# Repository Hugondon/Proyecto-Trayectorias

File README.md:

<h1 align="center">Proyecto de Ingeniería</h1>
<h2 align="center">Generación y Monitoreo de Trayectorias 3D sobre superficies regulares para Cobots UR</h2>

<!-- <h2>Herramientas Utilizadas</h2>

1. [MATLAB R2021b](#matlab)
2. [Python 3.8.10](#python)
3. [Polyscope](#polyscope)
4. [ESP-IDF](#esp-idf)

--- -->

<h2>Herramientas Utilizadas</h2>

<details>
<summary id="matlab">MATLAB R2021b</summary>
<h4>Procesamiento de Imagenes</h4>

Este modulo fue hecho especificamente para demostraciones.  
`Proyecto-Trayectorias\Software\MATLAB\Generacion_Trayectoria\Image_processing`: Path relativo al modulo para procesamiento de imagenes.  
En la carpeta `Imagenes` guarda la imagen que quieras procesar.  
Estas son las caracteristicas que mejoran el resultado del procesamiento de imagenes:

- Formato JPEG
- Imagenes caricaturescas
- Alto contraste entre fondo y objeto de interes

En el path `Proyecto-Trayectorias\Software\MATLAB\Generacion_Trayectoria\Image_processing` abre el script `prueba_imagen.m` es donde atraves de procesamiento de imagenes algoritmos de deteccion de bordes el objeto de una imagen se convierte en una trayectoria. Las variables que debes modificar de este script son las siguientes:

- `nameImage`: nombre de la imagen en la carpeta `Imagenes` la cual se quiere procesar.
- `physicalSize_m`: longitud del lado más largo del lienzo fisico del dibujo en metros. El programa en automatico expande o comprime la imagen, esto para que la longitud del lado más largo del dibujo digital coincida con la longitud del lado más largo del lienzo fisico.
- `reductionConstant`: numero de reducion de waypoints en la trayectoria. Que el robot no ejecute una trayectoria de más de 3000 waypoints, de preferencia mantente por debajo de 1,800 waypoints. Para reducir el numero de waypoints aumenta esta variable a tu discreción. La relación se expresa con la siguiente formula:  
  $length(outputTrajectory) = \lceil {\frac {length(originalTrajectory)} {reductionConstant}}\rceil$

- `numLowPointsThreshold`: los objetos con menos de esta cantidad de waypoints son eliminados. Por lo general se usa para eliminar puntos muy pequeños de la imagen.
- `numHighPointsThreshold`: los objetos con más de esta cantidad de waypoints son eliminados. Por lo general se usa para eliminar el marco de la imagen.
- `eliminatedObject`: el ID de un objeto que se quiere eliminar en especifico.

El resultado es guardado en el archivo `waypoints.mat`.

En el path `Proyecto-Trayectorias\Software\MATLAB\Generacion_Trayectoria` abre el script `imagePlacement.m` para que puedas apreciar el tamaño del dibujo con respecto al robot. Debido a que las poses son relativas con el primer waypoint de la trayectoria no importa la posicion u orientacion. Las poses son guardadas en `trajectoryPoses.mat` para posteriormente ser simulados con el robot.

<h4>Procesamiento de Modelos CAD</h4>

En el path `Proyecto-Trayectorias\Software\MATLAB\Generacion_Trayectoria\CAD_procesing` abre el script `cad_interactive_node_selector.m` es un selector interactivo de los nodos del modelo CAD.  
En la carpeta `Parts` guarda las piezas CAD en formato CSV.  
En la linea `gm=importGeometry(msd,'Part\botella.STL')` esta el Path para exportar el modelo CAD.  
En el apartado `Generate Mesh`:

- `edgeLenght.Hmax`: maxima longitud de una arista de la malla.
- `edgeLenght.Hmin`: minima longitud de una arista de la malla.  
  Modifica `edgeLenght.Hmax` y `edgeLenght.Hmin` a tu conveniencia, aristas muy pequeñas haran el programa muy lento, aristas muy grandes haran que se pierda resolución del modelo.  
  El modelo CAD y sus parametros es guardado en `CADparameters.mat` y las poses en latrayectoria del modelo CAD junto con el modelo CAD son guardados en `processedCAD.mat`.

En el path `Proyecto-Trayectorias\Software\MATLAB\Generacion_Trayectoria` esta el script `CADplacement.m` sirve para vizualizar el robot, el modelo CAD y la trayectoria sobre la superficie del modelo CAD. Además puedes modificar la pose del modelo CAD.  
En el apartado `Modifing Processed CAD` tienes las siguientes variables para modificar la pose del modelo CAD y la trayectoria en la superficie del modelo CAD:

- `displacementVector` : representa la posicion del modelo CAD y la trayectoria.
- `rotationVector` : representa la orientacion del modelo CAD y la trayectoria.  
  Importante: la posicion y orientacion del modelo CAD y la trayectoria sobre su superficie estan ligadas modificar `displacementVector` y `rotationVector` afectara a ambas.  
  El modelo CAD y la trayectoria en su superficie son guardados en `transformedCAD.mat`, para posteriormente ser simulados con el robot.

<h4>Simulacion del Robot</h4>

En el path `Proyecto-Trayectorias\Software\MATLAB\Generacion_Trayectoria` abre el script `main.m` Toma la trayectoria deseada, calcula la cinematica inversa, grafica la trayectoria y simula el robot. Ve a la subseccion `Get Waypoints` ahi podras definir de donde quieres que se obtenga la trayectoria. El numero en la variable `typeTrajectory` define cual trayectoria es utilizada.

| Número | Tipo de Trayectoria |
| ------ | ------------------- |
| 0      | Test Trajectory     |
| 1      | CAD Trajectory      |
| 2      | Image Trajectory    |

La funcion `simulateRobot` unicamente simula el movimiento del robot. Si es comentada esa linea no afecta el resultado.

El tipo de movimiento, las poses y las configuraciones del robot en la trayectoria son guardadas en el CSV `trajectory.csv` .

</details>

<details>
<summary id="python">Python</summary>
<h4> Parser </h4>

<p>

Este módulo se diseñó para llevar a cabo la conversión de la información contenida en el archivo `trajectory.csv` .

</p>

<p>

De forma general, el algoritmo para llevar a cabo esta tarea consiste en la iteración sobre las filas del archivo CSV para la extracción información de la pose y espacio de configuración y la generación del código .script a partir de esta.

</p>

<p>

Aprovechando que el lenguaje es orientado a objetos, se utilizó esto para encapsular información de los datos relevantes. La definición de estos se encuentra [aquí](https://github.com/Hugondon/Proyecto-Trayectorias/blob/main/Software/Python/utils/UR.py).

La información contenida en cada una de las filas del CSV se almacena en forma de listas de objetos (una para el Tipo de Movimiento y otra para las Poses). Al terminar de extraer toda la información, comienza el proceso de generación del código `.script` que será enviado al Robot. Esto se hace a través de la concatenación de strings conteniendo la información. Para ver directamente el funcionamiento de esto, ver la función `parse_csv` de [este](https://github.com/Hugondon/Proyecto-Trayectorias/blob/main/Software/Python/app.py) archivo.

</p>
<p>

Para la generación del código `.script` es importante mencionar que este se dividirá en dos partes:

`initialization`. Se utiliza para la inicialización de configuraciones en general (por el momento utilizado solamente para un contador global para llevar a cabo la trayectoria por una o más veces).

`main`. Aquí se encuentra en primer lugar la inicialización para llevar a cabo los movimientos de forma relativa al lugar en el que se encuentra actualmente el TCP y para llevar a cabo la información de la trayectoria

</p>

<p>

Todo esto se lleva a cabo como un programa debajo de una GUI, la cual se ejecuta con el siguiente comando:
`python .\Software\Python\app.py`
Es importante mencionar que este puede variar de acuerdo al Path desde el cual se ejecuta la aplicación, esto es considerando que se encuentra en el folder de `Proyecto-Trayectorias`)

El uso general de la GUI consiste en dos pasos:

1.  Seleccionar el archivo CSV con el que se desea generar el `.script` a través de la ventana que se abre cuando se presiona el botón `Load CSV File`

2.  Seleccionar el path en el cual se desea crear este archivo a través del uso del botón `Save to specific folder`

Como comentario adicional, el botón de `Save URScript File` es útil para guardar directamente el archivo después de una modificación en el path (el nombre del archivo, por ejemplo) sin tener que seleccionar el folder de nuevo desde la ventana.

Finalmente, en el [folder correspondiente a este módulo](https://github.com/Hugondon/Proyecto-Trayectorias/tree/main/Software/Python) se encuentra un archivo CSV de ejemplo. Se puede practicar con este, el archivo resultante debe verse de la siguiente forma al abrirse con Excel:

</p>

</details>

<details>
<summary id="polyscope">Polyscope</summary>
<h4>Instalación Polyscope en Ubuntu</h4>

Seguir tutorial en [este repositorio](https://github.com/arunavanag591/ursim) con las siguientes modificaciones:

1. Instalar Java con [este tutorial](https://tecadmin.net/install-oracle-java-8-ubuntu-via-ppa/)
2. Hacer cambio de curl en archivo `install.sh`:

`commonDependencies='libcurl4 openjdk-8-jre libjava3d-* ttf-dejavu* fonts-ipafont fonts-baekmuk fonts-nanum fonts-arphic-uming fonts-arphic-ukai'`

Ejemplo de `install.sh` en carpeta Polyscope.

<h4>Ejecutar programa en el Robot</h4>

TO-DO

</details>

<details>
<summary id="esp-idf">ESP-IDF</summary>

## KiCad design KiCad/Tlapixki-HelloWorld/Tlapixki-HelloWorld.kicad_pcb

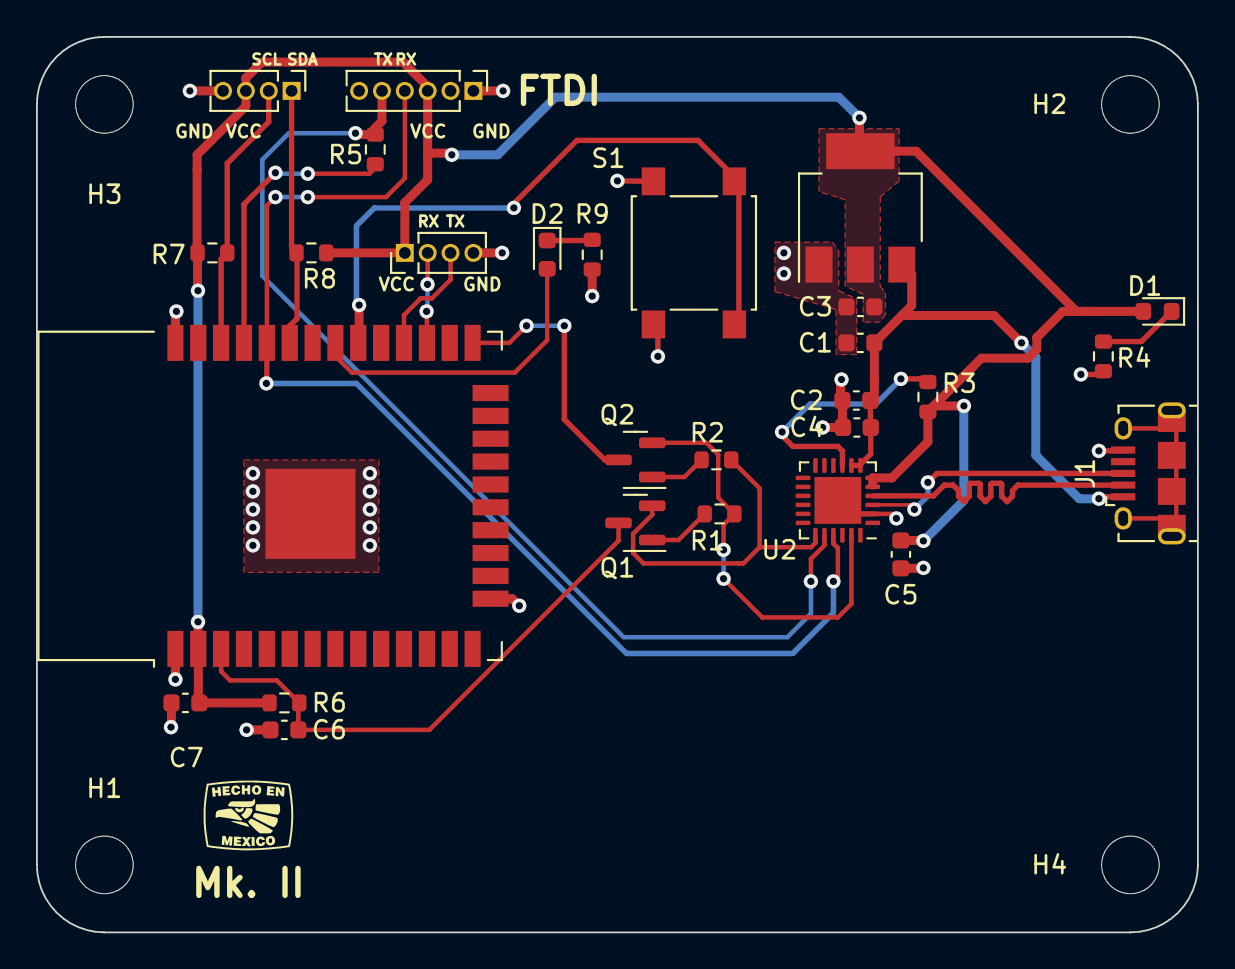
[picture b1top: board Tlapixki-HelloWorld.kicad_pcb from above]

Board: 2 copper layers, 64.5 x 49.8 mm, 32 parts (0 on the bottom side), 23 nets.

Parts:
C1, C3: 22u; C_0603_1608Metric
C2, C5, C7: 0.1u; C_0603_1608Metric
C4: 1u; C_0603_1608Metric
C6: 10u; C_0603_1608Metric
D1, D2: RED; LED_0603_1608Metric
H1, H2, H3, H4: MountingHole; MountingHole_3.2mm_M3
J1: USB_B_Micro; USB_Micro-B_Amphenol_10118194_Horizontal
J2: Conn_01x06_Female; PinHeader_1x06_P1.27mm_Vertical
J3, J4: Conn_01x04_Male; PinHeader_1x04_P1.27mm_Vertical
Q1, Q2: BC817; SOT-23
R1, R2, R6: 10k; R_0603_1608Metric
R3, R7, R8: 4k7; R_0603_1608Metric
R4, R9: 220; R_0603_1608Metric
R5: 470; R_0603_1608Metric
S1: SW_SPST; SW_SPST_B3S-1000
U1: AMS1117CD-3.3; SOT-223-3_TabPin2
U2: CP2102N-A02-GQFN24; QFN-24-1EP_4x4mm_P0.5mm_EP2.6x2.6mm
U3: ESP32-WROOM-32

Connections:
+3V3: C3.1, C5.1, C7.1, D1.2 (A), J2.3, J3.3, J4.1, R3.2, R6.1, R7.1, R8.1, U1.2 (VO), U2.5 (VIO), U2.6 (VDD), U3.2 (VDD)
/USB_D+: J1.3 (D+), U2.3 (D+)
/USB_D-: J1.2 (D-), U2.4 (D-)
DTR: Q2.2 (E), R1.1, U2.23 (~DTR)
EN: C6.1, Q1.3 (C), R6.2, U3.3 (EN)
GND: C1.2, C2.2, C3.2, C4.2, C5.2, C6.2, C7.2, J1.5 (GND), J2.1, J3.4, J4.4, R4.2, R9.2, S1.1 (A), U1.1 (GND), U2.2 (GND), U2.25 (GND), U3.1 (GND), U3.15 (GND), U3.38 (GND), U3.39 (GND)
GPIO0: Q2.3 (C), U3.25 (IO0)
GPIO18: S1.2 (B), U3.30 (IO18)
GPIO19: D2.2 (A), U3.31 (IO19)
unnamed: D1.1 (K), R4.1
unnamed: D2.1 (K), R9.1
unnamed: Q1.1 (B), R1.2
unnamed: Q2.1 (B), R2.2
unnamed: R3.1, U2.9 (~RST)
unnamed: R5.1, U3.35 (TXD0/IO1)
RTS: Q1.2 (E), R2.1, U2.19 (~RTS)
RX0: J2.4, U2.21 (TXD), U3.34 (RXD0/IO3)
RX2: J4.2, U3.27 (IO16)
SCL: J3.2, R7.2, U3.36 (IO22)
SDA: J3.1, R8.2, U3.33 (IO21)
TX0: J2.5, R5.2, U2.20 (RXD)
TX2: J4.3, U3.28 (IO17)
VBUS: C1.1, C2.1, C4.1, J1.1 (VBUS), U1.3 (VI), U2.7 (VREGIN), U2.8 (VBUS)

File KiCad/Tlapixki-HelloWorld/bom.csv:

Comment,Designator,Footprint,LCSC Part #,
22u Unpolarized capacitor,"C1,C3",C_0603_1608Metric,C41851,
0.1u Unpolarized capacitor,"C2,C5,C7",C_0603_1608Metric,C161854,
1u Unpolarized capacitor,C4,C_0603_1608Metric,C2857982,
10u Unpolarized capacitor,C6,C_0603_1608Metric,C2909630,
RED Light emitting diode,"D1,D2",LED_0603_1608Metric,C72037,
MountingHole Mounting Hole without connection,"H1,H2,H3,H4",MountingHole_3.2mm_M3,,
USB_B_Micro USB Micro Type B connector,J1,USB_Micro-B_Amphenol_10118194_Horizontal,C132563,
"Conn_01x06_Female Generic connector, single row, 01x06, script generated (kicad-library-utils/schlib/autogen/connector/)",J2,PinHeader_1x06_P1.27mm_Vertical,,
"Conn_01x04_Male Generic connector, single row, 01x04, script generated (kicad-library-utils/schlib/autogen/connector/)","J3,J4",PinHeader_1x04_P1.27mm_Vertical,,
"BC817 0.8A Ic, 45V Vce, NPN Transistor, SOT-23","Q1,Q2",SOT-23,C475629,
10k Resistor,"R1,R2,R6",R_0603_1608Metric,C98220,
4k7 Resistor,"R3,R7,R8",R_0603_1608Metric,C23162,
220 Resistor,"R4,R9",R_0603_1608Metric,C2907127,
470 Resistor,R5,R_0603_1608Metric,C2907172,
SW_SPST Single Pole Single Throw (SPST) switch,S1,SW_SPST_B3S-1000,C180420,
"AMS1117CD-3.3 1A Low Dropout regulator, positive, 3.3V fixed output, TO-252",U1,SOT-223-3_TabPin2,C498117,
"CP2102N-A02-GQFN24 USB to UART master bridge, QFN-24",U2,QFN-24-1EP_4x4mm_P0.5mm_EP2.6x2.6mm,C969151,
"ESP32-WROOM-32 RF Module, ESP32-D0WDQ6 SoC, Wi-Fi 802.11b/g/n, Bluetooth, BLE, 32-bit, 2.7-3.6V, onboard antenna, SMD",U3,ESP32-WROOM-32,C82899,

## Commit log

2021-08-24 Hello World en Script
2021-08-24 Se agrega archivo de tarea 1
2021-09-18 Tarea 1 + Avance
2021-09-24 Sincronizar con URSim
2021-09-24 Primera version de movimiento en MATLAB
2021-09-28 Calcula magnitud de distancia para obtener tiempo
2021-09-28 Se agrega getTrajectoryTimes
2021-09-28 Se agregó formato a programas
2021-09-28 Revision 27-09-21 (main)
2021-09-29 Reorganizar archivos URScript
2021-09-29 Escribir archivos CSV desde MATLAB
2021-09-29 Leer archivo CSV desde Python
2021-09-29 Avance correr script MATLAB
2021-09-29 Funciones comentadas
2021-09-29 Correr script MATLAB
2021-09-29 Primer avance para programa de parseo
2021-10-05 Carpeta PFI y de codigos de practica
    Se metieron todos los programas y archivos relacionados con el main a la carpeta PFI. Se agrego la carpeta de codigos de practica.
2021-10-05 Cambio nombre de PFI a Generacion__Trayectorias
    Cambio de nombre.
2021-10-05 primera escritura en Script
2021-10-05 generación de funciones + popup
2021-10-05 Agregar Graficar Trayectorias Incompleto 0
    Se agrego la posibilidad de agregar trayectorias. Se puede graficar trayectorias de los mainWaypoints en linea y los marcos de referencia. Todavia esta incompleto.
2021-10-05 primer approach a movel
2021-10-06 Agregar Graficar Trayectorias Incompleto 1
    Se optimizaron algunos aspectos pero todavia no se tiene el resultado deseado. Se grafican las trayectorias entre un main waypoint y de ahi se mueve el robot entre un main waypoint y otro. Lo que se 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
2021-10-06 Incorporación movej +movel
2021-10-06 Generación de cuadrado con diferentes movimientos
2021-10-06 Cambio en estructura del programa + get_integer
2021-10-06 Agregar typing
2021-10-06 Objeto ConfigurationSpace + cambio en __str__
2021-10-06 Generar sol y eolc de forma automática
2021-10-08 Primera versión de generación de Script
2021-10-08 Agregar información adicional a main del parser
2021-10-12 Actualización de importación de constantes
2021-10-12 Independencia de Path + While
2021-10-12 Librerías (?)
2021-10-12 Pose Calculation, Pose Graphing and Robot IK and Graphing was split.
    The processes of Pose calculation, Pose graphing and Robot Ik and Robot Graphing, was split between different for loops. A Cell Array was created to store type of movement, poses of trajectory and co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
2021-10-13 Inverse Kinematics and Robot Simulation was divided
    Inverse Kinematics and Robot Simulation was divided in two for loops for better readability.
2021-10-14 Escritura de MATLAB a archivo trajectory.csv
2021-10-19 Test Trajectories and alternate mode of setWaypoints
    Test Trajectories were added to test the algorithm. the function setWaypoints() now load the waypoints instead of declaring it in the program.
2021-10-20 CSV corrected and some anotations
    CSV convertion was corrected and some anotations where added
2021-10-21 Agregar tres nuevas trayectorias Hugo
2021-10-21 Agregar PPT guía para generar trayectoria
2021-10-29 Clear and moveL and simulateRobot Functions
    A Clear was added to clean some process variable or constants. The Function moveL and simulateRobot were added to both improve readability and modularity and to reduce crowding.
2021-11-06 Python compu Adrian y funcion moveL
    El programa de python ya funciona en la compu de Adrián. El moveL se convietio a una funcion.
2021-11-10 Whiteboard Trajectory
    Trajectories were adapted to write them in the whiteboard.
2021-11-11 Actualizar README
2021-11-11 Actualizar PNG
2022-01-31 Comments to all functions
    All the functions used in the project were commented.
2022-01-31 Test Files Eliminated
    Files used for prove of concept were deleted.
2022-03-29 CAD model import and CAD post-processing
    CAD model Import
    1-A CAD model saved as an .stl can be exported as a PDE model.
    2-PDE model can be turn in a Discrete Geometric Model.
    3-Discrte Geometric model can be turn to a Mesh.
    Verification Mesh and robot model
    4-Mesh and robot model can be in the same Figure.
2022-04-03 Interactive point selection
    Points can be selected interactively on the CAD, but selection is inaccurate in some faces of the CAD.
2022-04-04 Improved interactive point selection
    -Points in surface of CAD can be selected realiably.
    -Points selected can saved in memory.
    -Points selected can be ploted for visual feedback for the user.
2022-04-05 Ordering and beginnning surface path planning
    -Get the IDs of the nodes which correspond to each face.
    -Get the centroid of each face.
    -Order
2022-04-12 Commentary and convert2csv function
    -Commentary was added
    -New function that turns "trajectory data" in csv format
2022-04-17 Surface Path planning
    Additions
    -Surface paths are obtain.
    -Surface path are plotted.
    -ID of the nodes in the surface path is saved.
    Still Pending:
    -Get normal vector and know if it point in or out.
2022-04-18 Commentary
    -Commentary missing from the previous commit was added.
2022-04-19 Beginning Normal Vertex
    Additions:
    -Calculate normal vertex from almost all nodes.
    Pending:
    -Calculate Normal Vertex
    -Manage to obtain surface nodes from shared nodes
2022-04-24 Pose calculation for Trajectories
    -Unit Normal Vertex function added.
    -Unit Tangential Vertex function added.
    -Node Pose calculation added.
2022-04-25 Exporting Results of CAD processing
    -Save Geometric Model.
    -Save Poses of the Trajectory.
    -Placement Script to make sure GeometricModel is it a good position.
2022-04-25 CAD Model Trajectory Simulation
    -Geometric model, its Reference Frame and the Surface Trajectory now can be exported to the main.
    -Transformation to adjust the tool pose to the CAD trajectory pose was added.
    -Script to verify placement of the CAD with respect to the robot was added.
    -Script to transform Discrete Geometry, its Reference Frame an the Trajectory was added.
    -Duplicate Nodes IDs in the "nodesTrajectoryInSurfaceID.csv" file defect was removed.
    -In the main now there is the option to use a test trajectory or a CAD trajectory.
2022-04-25 Commit for test
2022-04-26 Agregar Mk II de PCB
2022-04-27 Version Inicial de Proyecto
2022-04-27 HTTP Server
2022-04-28 Wi Fi Connection (no testeado)
2022-05-05 Ejemplos funcionales de ethernet + TCP
2022-05-05 GUI Primera Versión
2022-05-05 Refactor Archivos Python
2022-05-05 GUI 2.0
2022-05-06 Bottle model
    -Bottle model was included
2022-05-06 Unused models
2022-05-07 Modbus Master funcional :)
2022-05-07 Flask App - Basic Code
2022-05-07 Adding templates
2022-05-07 Adding templates 2
2022-05-07 Git Ignore
2022-05-08 Fixed server
2022-05-09 Actualizacion para movimiento relativo
2022-05-09 Corrección paréntesis
2022-05-09 Corrección :)
2022-05-10 WiFi + Ethernet!
2022-05-14 Firmware version 0.1 - TCP Multiple Clients
2022-05-14 Firmware Version 0.2 - Get implementado
2022-05-15 Firmware Version 0.3 - Get + Modbus Concurrentes
2022-05-15 Firmware Version 0.4 - configurations.h
2022-05-16 Firmware Version 0.5-POST a Servidor (hardcoded)
2022-05-16 Fixed data.py
2022-05-16 Fixed post
2022-05-16 Fixed json
2022-05-16 Fixed json structure
2022-05-16 Version Firmware 0.6 - Actualizar JSON
2022-05-16 Firmware Version 0.7 - Ethernet + POST funcional
2022-05-17 Actualizar GUI (ícono)
2022-05-19 Javascript Firebase API
2022-05-19 Flask Server
2022-05-20 Reorganizaciòn General del Proyecto
2022-05-21 Image processing
2022-05-26 Corrección en get de API
2022-05-26 Firmware Version 1.0 - Funcional
2022-08-13 Images to Draw added
    Images for the robot to draw were added.
2022-08-14 Actualizacion
2022-08-15 Documentación para Módulo de Python
2022-08-15 Corrección de Módulo de Python
2022-08-17 User selected variables added
    1-User selected variable sections were added to 3 important files:
    -main.m
    -prueba_imagen.m
    -cad_interactive_node_selector.m
    This was made to make easier the modification of the variables for new users.
    2-Unnecesary Folder was eliminated.
2022-08-17 Minor change in
    imagen_prueba.m
2022-10-25 Path correction
    Paths in the path were changed to be able to run it.
2022-10-25 Logos
    Se dibujaron logos de empresas para demostracion.
2022-10-26 Bug Fix
    The inverted backslash character "\" was wrongly replaced by backslash character "/". That error has been fixed.
2023-03-31 Images Added
    Images added for the image drawing
